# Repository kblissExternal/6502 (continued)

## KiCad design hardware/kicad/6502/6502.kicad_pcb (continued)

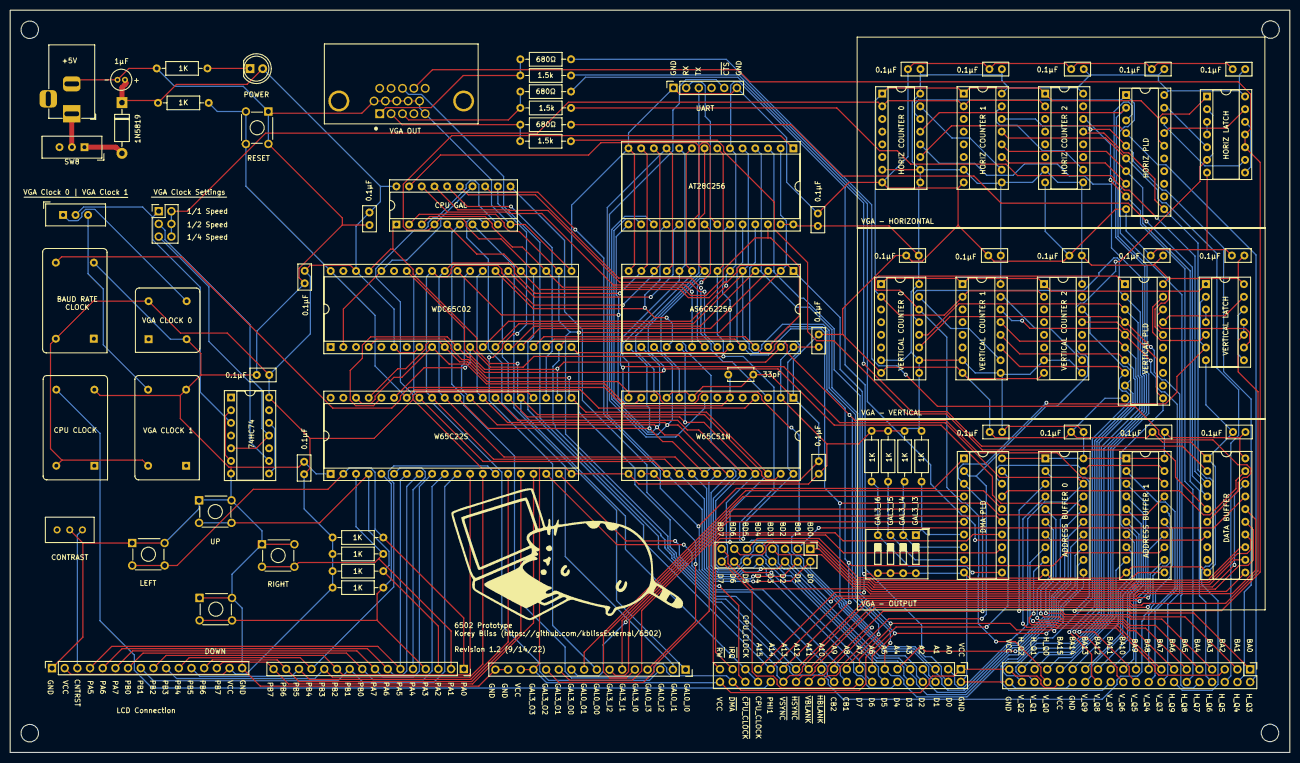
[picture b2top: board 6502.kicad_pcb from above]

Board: 2 copper layers, 256.3 x 148.7 mm, 89 parts (0 on the bottom side), 164 nets.

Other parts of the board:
NE: MountingHole_3.5mm
NW: MountingHole_3.5mm
SE: MountingHole_3.5mm
SW: MountingHole_3.5mm

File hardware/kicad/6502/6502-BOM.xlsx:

Ref | Qnty | Value | Cmp name | Cmp Purchase | Footprint | Footprint Purchase | Description
C1, | 1.0 | 1µF | C | https://mou.sr/3RYvaGw | Capacitor_THT:C_Radial_D4.0mm_H5.0mm_P1.50mm |  | Unpolarized capacitor
C2, C3, C4, C5, C6, C7, C8, C9, C10, C12, C13, C14, C15, C16, C17, C18, C19, C2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 | 21.0 | 0.1µF | C | https://mou.sr/3L92t7l | Capacitor_THT:C_Disc_D5.0mm_W2.5mm_P2.50mm |  | Unpolarized capacitor
C11, | 1.0 | 33pF | C | https://mou.sr/3Uc47cD | Capacitor_THT:C_Disc_D5.0mm_W2.5mm_P5.00mm |  | Unpolarized capacitor
D1, | 1.0 | 1N5819 | 1N5819 | https://mou.sr/3BAfBiO | Diode_THT:D_DO-41_SOD81_P10.16mm_Horizontal |  | 40V 1A Schottky Barrier Rectifier Diode, DO-41
D2, | 1.0 | LED | LED |  | LED_THT:LED_D5.0mm |  | Light emitting diode
J1, | 1.0 | Barrel_Jack | Barrel_Jack | https://mou.sr/3eDGF7P | Connector_BarrelJack:BarrelJack_Horizontal |  | DC Barrel Jack
J2, | 1.0 | Bus_Header | Conn_02x20_Odd_Even | https://mou.sr/3do1bsG | Connector_PinHeader_2.54mm:PinHeader_2x20_P2.54mm_Vertical |  | Generic connector, double row, 02x20, odd/even pin numbering scheme (row 1 odd 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
J3, | 1.0 | LCD_Header | Conn_01x16_Female | https://mou.sr/3RRFn7V | Connector_PinSocket_2.54mm:PinSocket_1x16_P2.54mm_Vertical |  | Generic connector, single row, 01x16
J4, | 1.0 | UART_Header | Conn_01x06_Female | https://mou.sr/3BaX7UI | Connector_PinSocket_2.54mm:PinSocket_1x06_P2.54mm_Vertical |  | Generic connector, single row, 01x06
J5, | 1.0 | VIA_Header | Conn_01x16_Female | https://mou.sr/3RRFn7V | Connector_PinSocket_2.54mm:PinSocket_1x16_P2.54mm_Vertical |  | Generic connector, single row, 01x16
J6, | 1.0 | VGA_Out | DB15_Female_HighDensity | https://mou.sr/3U9t1cS | VGA:TE_1-1734530-1 |  | 15-pin female D-SUB connector, High density (3 columns), Triple Row, Generic, V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
J7, | 1.0 | GAL_Header | Conn_01x16_Female | https://mou.sr/3QNGOmm | Connector_PinSocket_2.54mm:PinSocket_1x16_P2.54mm_Vertical |  | Generic connector, single row, 01x16
J8, | 1.0 | VGA_Address_Header | Conn_02x20_Odd_Even | https://mou.sr/3do1bsG | Connector_PinHeader_2.54mm:PinHeader_2x20_P2.54mm_Vertical |  | Generic connector, double row, 02x20
J9, | 1.0 | VGA_Clock | Conn_02x03_Odd_Even | https://mou.sr/3UbDc0q | Connector_PinHeader_2.54mm:PinHeader_2x03_P2.54mm_Vertical |  | Generic connector, double row, 02x03
J10, | 1.0 | VGA_Data_Header | Conn_02x08_Odd_Even | https://mou.sr/3Dn1XRw | Connector_PinHeader_2.54mm:PinHeader_2x08_P2.54mm_Vertical |  | Generic connector, double row, 02x08, odd/even pin numbering scheme (row 1 odd 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
R1, R2, R3, R4, R5, R6, R13, R14, R15, R16, | 10.0 | 1k | R_US | https://mou.sr/3xhN8M1 | Resistor_THT:R_Axial_DIN0207_L6.3mm_D2.5mm_P10.16mm_Horizontal |  | Resistor, US symbol
R7, R9, R11, | 3.0 | 680.0 | R_US | https://mou.sr/3qEoBgq | Resistor_THT:R_Axial_DIN0207_L6.3mm_D2.5mm_P10.16mm_Horizontal |  | Resistor, US symbol
R8, R10, R12, | 3.0 | 1.5k | R_US | https://mou.sr/3qJ1EZL | Resistor_THT:R_Axial_DIN0207_L6.3mm_D2.5mm_P10.16mm_Horizontal |  | Resistor, US symbol
RV1, | 1.0 | R_Potentiometer | R_Potentiometer | https://mou.sr/3S83Aqs | Potentiometer_THT:Potentiometer_Bourns_3386C_Horizontal |  | Potentiometer
SW1, SW2, SW3, SW4, SW5, | 5.0 | SW_Push | SW_Push | https://mou.sr/3eIzPy2 | Button_Switch_THT:SW_TH_Tactile_Omron_B3F-10xx |  | Push button switch, generic, two pins
SW6, | 1.0 | SW_VGA_CLOCK | SW_SPDT | https://mou.sr/3U40nK1 | Switch:SW_THT_DPDT |  | Switch, single pole double throw
SW7, | 1.0 | DMA_DIP | SW_DIP_x04 | https://mou.sr/3QRpygp | Button_Switch_THT:SW_DIP_SPSTx04_Slide_9.78x12.34mm_W7.62mm_P2.54mm |  | 4x DIP Switch, Single Pole Single Throw (SPST) switch, small symbol
SW8, | 1.0 | SW_SPDT | SW_SPDT | https://mou.sr/3U40nK1 | Switch:SW_THT_DPDT |  | Switch, single pole double throw
U1, U7, U9, U12, | 4.0 | GAL16V8 | GAL16V8 | https://mou.sr/3qwJien | Package_DIP:DIP-20_W7.62mm_Socket | https://mou.sr/3defX5i | Programmable Logic Array, DIP-20/SOIC-20/PLCC-20
U2, | 1.0 | W65C02SxP | W65C02SxP | https://mou.sr/3Dkbt7V | Package_DIP:DIP-40_W15.24mm_Socket | https://mou.sr/3qH9jaO | W65C02S 8-bit CMOS General Purpose Microprocessor, DIP-40
U3, | 1.0 | 28C256 | 28C256 | https://mou.sr/3RUXglV | Package_DIP:DIP-28_W15.24mm_Socket | https://mou.sr/3BkyTHw | Paged Parallel EEPROM 256Kb (32K x 8), DIP-28/SOIC-28
U4, | 1.0 | HM62256BLP | HM62256BLP | https://mou.sr/3qzRFG5 | Package_DIP:DIP-28_W15.24mm_Socket | https://mou.sr/3LexIOA | 32,768-word Ã— 8-bit High Speed CMOS Static RAM, 70ns, DIP-28
U5, | 1.0 | W65C22SxP | W65C22SxP | https://mou.sr/3RH02f0 | Package_DIP:DIP-40_W15.24mm_Socket | https://mou.sr/3qH9jaO | W65C22S CMOS Versatile Interface Adapter (VIA), 20-pin I/O, 2 Timer/Counters, D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
U6, U11, U18, U19, U20, U21, | 6.0 | 74LS161 | 74LS161 | https://mou.sr/3BzZZfc | Package_DIP:DIP-16_W7.62mm_Socket | https://mou.sr/3xt2Q7o | Synchronous 4-bit programmable binary Counter
U8, | 1.0 | W65C51NxP | W65C51NxP | https://mou.sr/3B4roEC | Package_DIP:DIP-28_W15.24mm_Socket | https://mou.sr/3LexIOA | W65C51N CMOS Asynchronous Communication Interface Adapter (ACIA), Serial UART, 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
U10, U13, | 2.0 | 74HC00 | 74HC00 | https://mou.sr/3BgiB2x | Package_DIP:DIP-14_W7.62mm_Socket | https://mou.sr/3DAlE8i | quad 2-input NAND gate
U14, | 1.0 | 74HC74 | 74HC74 | https://mou.sr/3RKX1tT | Package_DIP:DIP-14_W7.62mm_Socket | https://mou.sr/3DAlE8i | Dual D Flip-flop, Set & Reset
U15, U16, U17, | 3.0 | 74HC245 | 74HC245 | https://mou.sr/3U6tr3P | Package_DIP:DIP-20_W7.62mm_Socket | https://mou.sr/3defX5i | Octal BUS Transceivers, 3-State outputs
X1, X2, X4, | 3.0 | TFT680 | TFT680 | https://mou.sr/3RDGI29 | Oscillator:Oscillator_DIP-14 | https://mou.sr/3DAfghk | Crystal Clock Oscillator, DIP14-style metal package
X3, | 1.0 | TFT660 | TFT660 | https://mou.sr/3qGWkpK | Oscillator:Oscillator_DIP-8 | https://mou.sr/3Uf4zXu | Crystal Clock Oscillator, DIP8-style metal package

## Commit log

2022-08-23 Initial import.
2022-08-24 End of day 8/24.
2022-08-30 Added final hardware files for revision 1.0.
2022-08-30 Switched symon values back to hardware.
2022-08-30 Updated README with EH Basic info.
2022-08-30 Updated README.
2022-08-30 Moved VGA constants to VGA specific file.
2022-08-31 Added simple monitor.
2022-08-31 Correced menu issues.
2022-09-02 Corrected some minor rev 1.0 issues.
2022-09-03 Update to Revision 1.1 (primarily adding 6551).
2022-09-04 Corrected button values to match new hardware build.
2022-09-13 Added VGA testing components.
2022-09-15 Finalized revision 1.2.
2022-09-15 BOM updates.
2022-09-25 Baseline for VGA functionality.
2022-11-01 Added current VGA hardware and code.
2022-11-11 Code fixes.
